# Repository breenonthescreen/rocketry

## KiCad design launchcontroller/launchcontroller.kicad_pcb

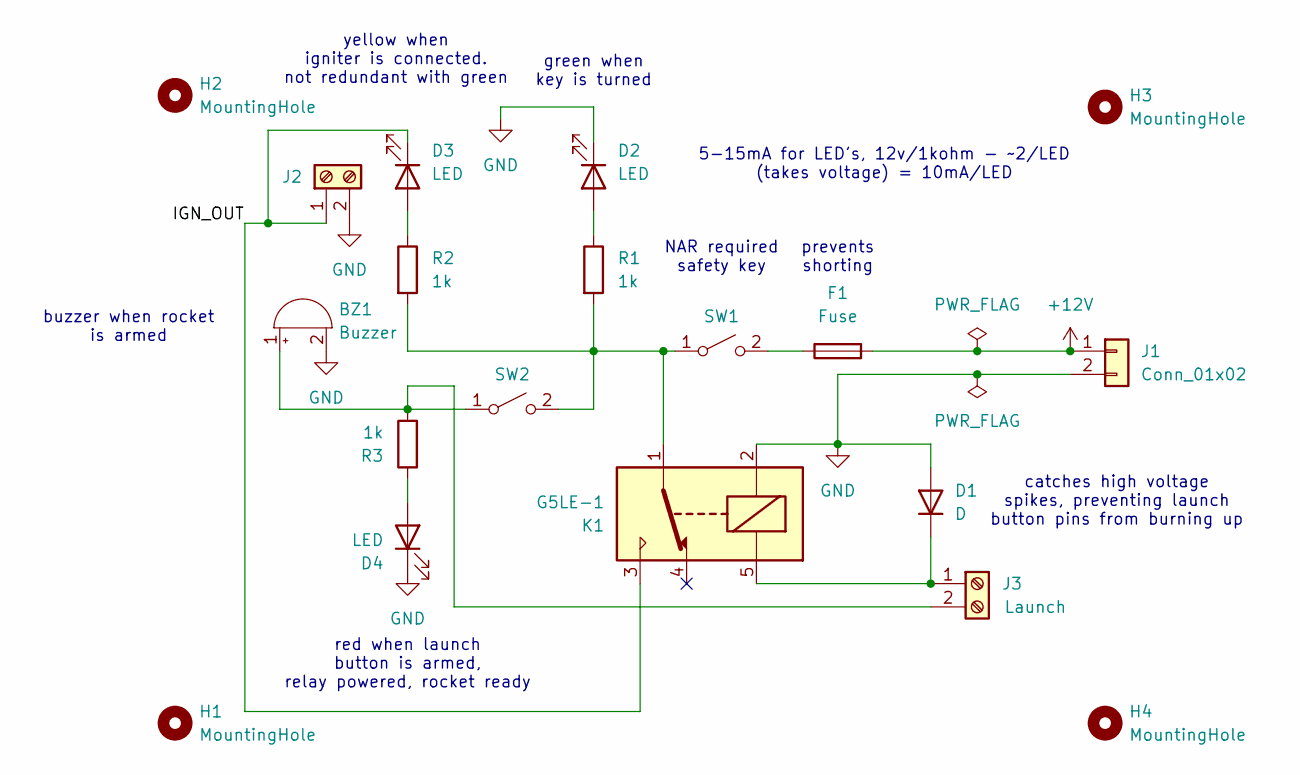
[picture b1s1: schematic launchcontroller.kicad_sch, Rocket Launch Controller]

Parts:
BZ1: Buzzer; Buzzer_12x9.5RM7.6
D1: D; D_DO-41_SOD81_P10.16mm_Horizontal
D2, D3, D4: LED; LED_D5.0mm
F1: Fuse; Fuseholder_Cylinder-5x20mm_Schurter_0031_8201_Horizontal_Op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
H1, H2, H3, H4: MountingHole; MountingHole_3.2mm_M3
J1: Conn_01x02; TerminalBlock_Phoenix_MKDS-1,5-2-5.08_1x02_P5.08mm_Horizont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
J2: Screw_Terminal_01x02; TerminalBlock_Phoenix_MKDS-1,5-2-5.08_1x02_P5.08mm_Horizont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
J3: Launch; TerminalBlock_Phoenix_MKDS-1,5-2-5.08_1x02_P5.08mm_Horizont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
K1: G5LE-1; Relay_SPDT_Omron-G5LE-1
R1, R2, R3: 1k; R_Axial_DIN0207_L6.3mm_D2.5mm_P10.16mm_Horizontal
SW1: KEY; TerminalBlock_Phoenix_MKDS-1,5-2-5.08_1x02_P5.08mm_Horizont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
SW2: ARM; TerminalBlock_Phoenix_MKDS-1,5-2-5.08_1x02_P5.08mm_Horizont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

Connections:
+12V: F1.2, J1.1
/IGN_OUT: D3.1 (K), J2.1, K1.3
GND: BZ1.2 (-), D1.2 (A), D2.1 (K), D4.1 (K), J1.2, J2.2, K1.2
unnamed: BZ1.1 (+), J3.2, R3.2, SW2.1 (A)
unnamed: D1.1 (K), J3.1, K1.5
unnamed: D2.2 (A), R1.1
unnamed: D3.2 (A), R2.1
unnamed: D4.2 (A), R3.1
unnamed: K1.1, R1.2, R2.2, SW1.1 (A), SW2.2 (B)
unnamed: F1.1, SW1.2 (B)

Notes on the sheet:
catches high voltage spikes, preventing launch button pins from burning up
buzzer when rocket is armed
red when launch button is armed, relay powered, rocket ready
NAR required safety key
yellow when igniter is connected. not redundant with green
green when key is turned
5-15mA for LED's, 12v/1kohm - ~2/LED (takes voltage) = 10mA/LED
prevents shorting

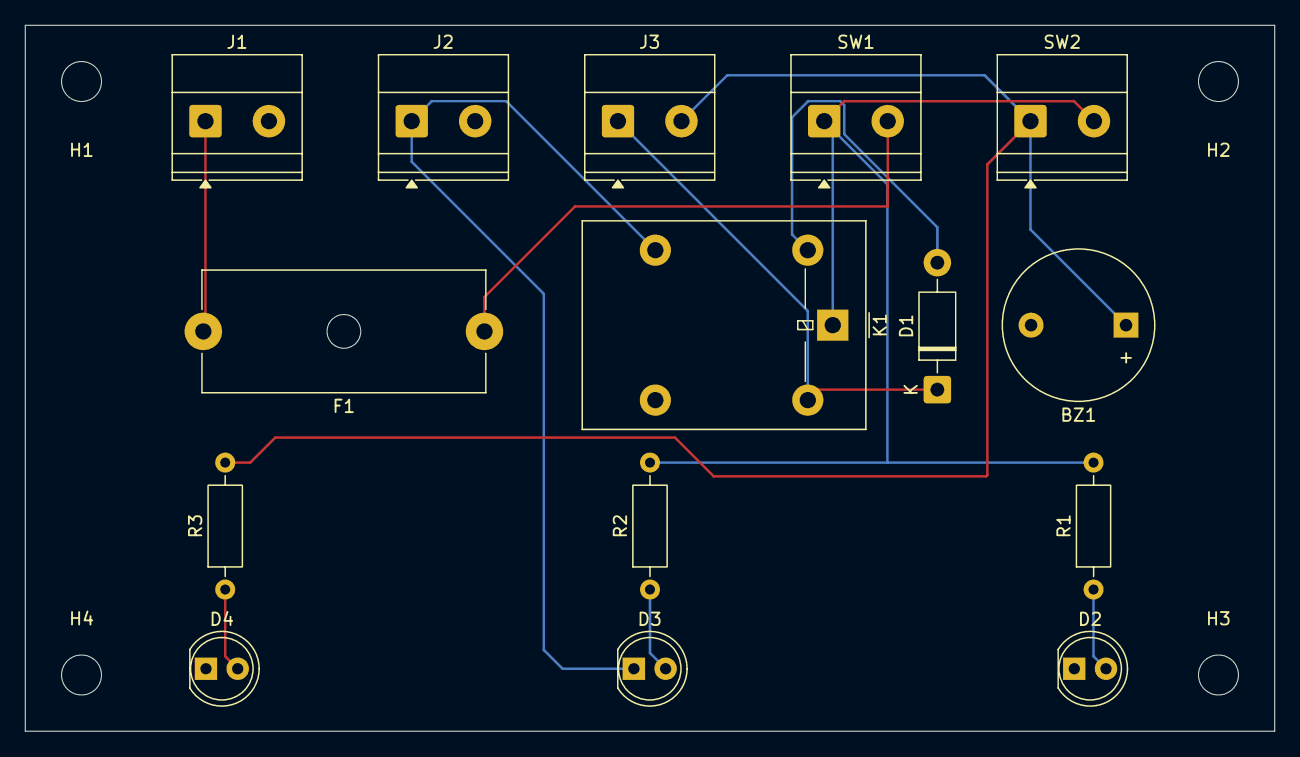
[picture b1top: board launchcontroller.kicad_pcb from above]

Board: 2 copper layers, 100.0 x 56.5 mm, 19 parts (0 on the bottom side), 10 nets.
